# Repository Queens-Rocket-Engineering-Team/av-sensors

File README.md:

# QRET Avionics (2025-2026)

This repository is the working space for QRET's 2025-2026 Avionics sensor breakout boards. This just includes hardware design for now.

If you're contributing, **make a branch first.**

Currently we're using KiCAD 8.0.6.

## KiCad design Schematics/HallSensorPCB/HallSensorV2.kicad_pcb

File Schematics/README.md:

# Schematics

This directory contains all schematics involved communicating with sensors external to Avionics SRAD PCBs.

## Hall Sensor
- Breakout board for a hall effect sensor 
- Designed for reading state of fill/vent/dump valves in the 2026 hybrid rocket

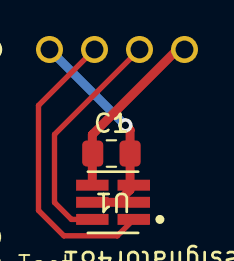
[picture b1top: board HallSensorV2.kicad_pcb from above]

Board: 2 copper layers, 3 parts (1 on the bottom side), 4 nets.

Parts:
C1: 0.01uF; C_0805_2012Metric_Pad1.18x1.45mm_HandSolder
J2: Conn_01x04_Pin; CONN_B04B-XASK-1_JST
U1: TMAG5273A1QDBVT; DBV0006A-IPC_A

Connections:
+3V3: C1.1, J2.4, U1.4 (VCC)
GND: C1.2, J2.1, U1.2 (TEST), U1.3 (GND), U1.5 (INT_N)
SCA: J2.3, U1.6 (SDA)
SCL: J2.2, U1.1 (SCL)

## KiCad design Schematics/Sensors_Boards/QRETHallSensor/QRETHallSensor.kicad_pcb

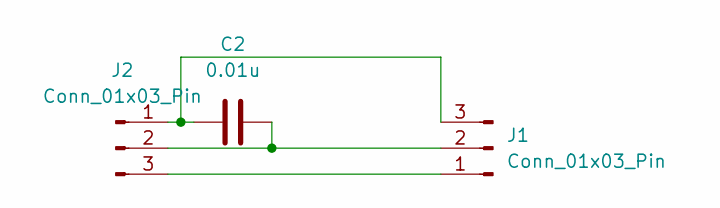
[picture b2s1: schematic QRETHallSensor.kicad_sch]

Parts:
C2: 0.01u; C_Radial_D8.0mm_H7.0mm_P3.50mm
J1: Conn_01x03_Pin; FanPinHeader_1x03_P2.54mm_Vertical
J2: Conn_01x03_Pin; LPG0003A

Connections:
unnamed: J1.1, J2.3
unnamed: C2.2, J1.2, J2.2
unnamed: C2.1, J1.3, J2.1

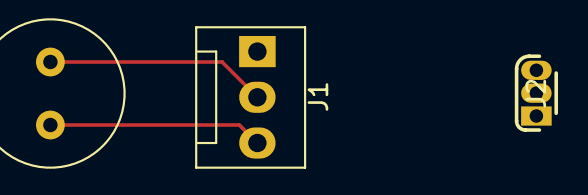
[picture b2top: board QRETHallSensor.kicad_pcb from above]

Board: 2 copper layers, 3 parts (0 on the bottom side), 3 nets.

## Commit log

2025-03-18 Several schematic improvements
    - Removed initial redundant reverse-polarity-protection and added clamping diodes for affected ADC inputs (should reduce cost & part count)
    - Updated contributor list
    - Added missing part numbers
    - Added switched 12V AUX output
    - Added lid sensor input
    - Changed some connectors to be smaller
2025-03-19 Added ATC fuse
    Also fixed wrong part number
2025-03-19 Added missing part numbers
2025-03-21 Updated incorrect SWD part number
2025-05-16 Finalized PCB layout
2025-05-16 Fixed silkscreen errors, adjusted trace sizes
2025-05-26 Updated pinout for comms module Rev2 (WAGGLE)
2025-05-26 Replaced RFM95 driver code with SX1262 driver code
    Adjusted the radiolib code from RFM95 driver to SX1262 driver. Also tried to adjust to using the new hardware USB peripherals, but found hardware problem where TX/RX were swapped by accident. Adjuste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
2025-06-03 Live Camera Rough Draft
2025-06-03 Quick cleanup
2025-06-04 Tweaked to make functional on Rev2 NASONOV module
    - Updated pinouts.h
    - Adapted code to work with new buzzer (still needs work)
    - Switched from softserial to proper hardware serial for USB
2025-06-05 Added callsign broadcast to packet
2025-06-06 Updated Altimeter Code
    Changed libraries and pinouts, finished state switch code. Need to finish the power save mode, as well as fix error with accelerometer - not currently able to connect to it with current code (could b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
2025-06-06 Add ability to tweak RF settings realtime over serial
    Should likely remove this before flight to ensure no accidental frequency changes are even possible
2025-06-06 Increased default TX power to 20db
2025-06-08 Updated CANPackets.h files
2025-06-09 Updated Comms mod for callsign and broadcast for SRAD ok
2025-06-09 added global var
2025-06-09 Proper buzzer driver implementation (untested)
    Now uses TIM1 in complementary mode to drive both BUZZER_A_PIN and BUZZER_B_PIN exactly inverse to eachother (with a deadtime between them to prevent shootthrough). This should effectively double the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
2025-06-09 Added TIM1_CH3 lines for ease of portibility
2025-06-10 Livecamera logic update
2025-06-10 Updated Live Camera Buzzer
2025-06-10 velocity code
2025-06-10 Buzzer code update
2025-06-10 Now reads callsign from packet, plus added radio config buttons
2025-06-10 Make rocketVelocity a double & added note
2025-06-10 Updated Buzzer Code
2025-06-11 change to feet
2025-06-11 Exposed VerticalVelocity on debug endpoint, updated pages
    Also improved unit consistency; all altitudes should be stored and worked with as METERS, and only converted to feet on the frontend. This was already mostly the case and the frontend erroneously dis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
2025-06-12 Revert "Buzzer code update"
    This reverts commit 8d92e3a1cc30204c7f2c19b12dd361adfffd2d17.
2025-06-12 sleep please
2025-06-12 COMPILED CURRENT VERSION TO BINARY
2025-08-04 Readd Buzzer Code
2025-08-04 Updated Settings and Comments
2025-08-04 Updated Settings
2025-08-04 Updated Date
2025-08-04 Updated CANBUS Packets
2025-08-04 New Sensors Code
2025-08-13 Base Binary
2025-08-16 Updated Altimeter
2025-08-17 Kx134 solve maybe?
2025-08-17 KX134 attempt #2
2025-08-17 need more input
2025-08-17 updated detection
2025-08-17 reversion
2025-08-17 Another attempt
2025-08-17 minor changes
2025-08-18 last chance
2025-09-03 remove sensor testing binary
2025-09-03 cleanup script, remove unused code
2025-09-20 Reverted Unnecessary Details
2025-09-20 updated spacing
2025-10-02 Fixed gps pin naming
2025-10-05 Update project timeline to 2023-2026
2025-11-27 initial hall effect sensor schematic
2025-11-29 Hall Effect Sensor Schematic and PCB
    The final PCB design for the Hall effect sensor. There are 6 copies of the PCB in the PCB file for making 6 at a time.
2026-01-11 Prepare branch for importing into dedicated sensor board repo
2026-01-14 Create Hall Sensor PCB V2
2026-01-18 Update hall schematic and pcb - add exact sensor schematic, models, etc - rerouted traces
